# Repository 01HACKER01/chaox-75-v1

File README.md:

# chaox-75-v1

## What is this
This is a keyboard based on rp2040 with only wired connection and it has 82 keys and a rotary encoder.

## Why does this exits
i have a evofox keyboard which costs $10 i got it from a friend i used it for a long time but now teh keys sometimes doesnt work or doesnt press or something and i thought that lets make a keyboard so thats how this keyboard came to light. 

## How to assemble
u just have to solder all the things to the pcb and for that u will need a hot air gun for smalll capacittors and the mcu and a soldering iron to solder all the switches and rotary encoder.

## How to flash 
1. plug in your RP2040 board while holding the BOOT button.

2. Drag and drop the official Pico .uf2 firmware into the RPI-RP2 drive.
to check if this worked check The drive will reboot and reappears as CIRCUITPY.

3. Copy the kmk folder and main.py script from teh firmware folder straight into the root of CIRCUITPY.

thats it done. 

## Bill of Materials (BOM)

| Part | Qty | Approx. USD | Link |
|---|---:|---:|---|
| **RP2040 MCU** (QFN-56) | 1 | $1.20 | [Alibaba](https://www.alibaba.com/trade/search?SearchText=RP2040+QFN56) |
| **W25Q16JV SPI Flash** (SOIC-8) | 1 | $0.40 | [Alibaba](https://www.alibaba.com/trade/search?SearchText=W25Q16JV) |
| **MCP1700-3302E** 3.3V LDO | 1 | $0.35 | [Alibaba](https://www.alibaba.com/trade/search?SearchText=MCP1700T-3302E) |
| **12 MHz SMD Crystal** (3225 4-pin) | 1 | $0.25 | [Alibaba](https://www.alibaba.com/trade/search?SearchText=12MHz+3225+crystal) |
| **Type-C 16-Pin Receptacle** | 1 | $0.30 | [Alibaba](https://www.alibaba.com/trade/search?SearchText=USB-C+16P+receptacle) |
| **Kailh MX Hot-Swap Sockets** | 82 | $6.50 | [Alibaba](https://www.alibaba.com/trade/search?SearchText=Kailh+MX+hot+swap+socket) |
| **SK6812 MINI-E RGB LEDs** | 82 | $6.00 | [Alibaba](https://www.alibaba.com/trade/search?SearchText=SK6812MINI-E) |
| **1N4148W Switching Diodes** (SOD-123) | 82 | $1.50 | [Alibaba](https://www.alibaba.com/trade/search?SearchText=1N4148W+SOD-123) |
| **Passives (0603 Caps & Resistors)** | ~88 pcs | $2.50 | [Alibaba](https://www.alibaba.com/trade/search?SearchText=0603+smd+resistor+capacitor+pack) |
| **EC11 Rotary Encoder + Knob** | 1 | $1.00 | [Alibaba](https://www.alibaba.com/trade/search?SearchText=EC11+rotary+encoder) |
| **SMD Tactile Push Buttons** (Reset/Boot) | 2 | $0.30 | [Alibaba](https://www.alibaba.com/trade/search?SearchText=SMD+tactile+push+button) |
| **Mechanical Switches (82-90 pcs pack)** | 1 pack (90 pcs) | $20.00–$32.00 | [Alibaba](https://www.alibaba.com/trade/search?SearchText=Gateron+Kailh+switches+90pcs) |
| **82-Key Compatible Keycap Set** | 1 set | $15.00–$25.00 | [Alibaba](https://www.alibaba.com/trade/search?SearchText=75+percent+keycaps) |
| **Plate/PCB-Mount Stabilizers** (3x 2u, 1x 6.25u) | 1 set | $4.00–$8.00 | [Alibaba](https://www.alibaba.com/trade/search?SearchText=keyboard+stabilizers+set) |
| **Custom PCB Fabrication** (5 pcs, JLCPCB 2-layer) | 5 pcs | $15.00–$25.00 | [JLCPCB](https://jlcpcb.com) |
| **Case & Switch Plate** (3D printed / CNC / Acrylic stack) | 1 | $15.00–$35.00 | [JLCPCB 3D Print](https://jlcpcb.com/3d-printing) |

### 💰 Total Cost Breakdown

| Category | Estimated Cost |
|---|---:|
| **PCB Components & Electronics** | ~$20 |
| **Switches (82 pcs), Keycaps & Stabs** | ~$40–$65 |
| **PCB Fab (JLCPCB + shipping)** | ~$15–$25 |
| **Case & Switch Plate (3D Printed / CNC)** | ~$15–$35 |
| **Total Build Cost** | **~$90–$200** |

## END
i guess thats it so thank you bye

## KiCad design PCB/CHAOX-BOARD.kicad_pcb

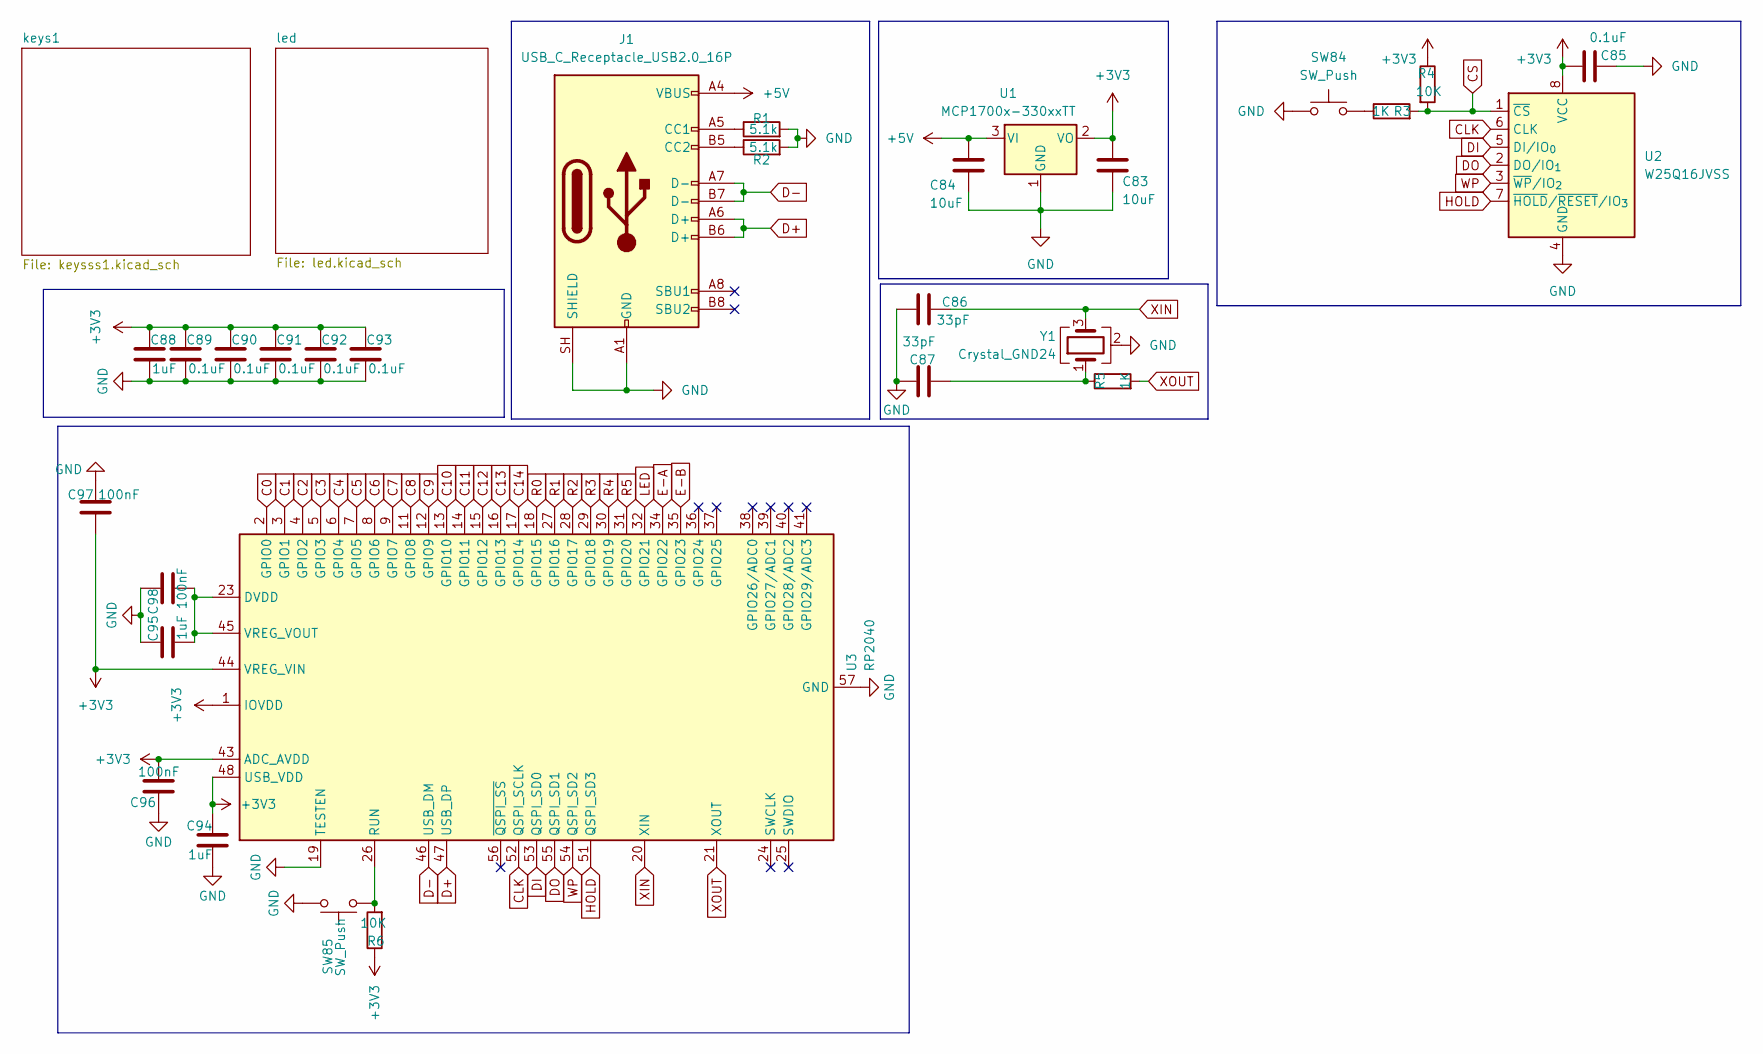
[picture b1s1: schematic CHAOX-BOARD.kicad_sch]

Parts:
C83, C84: 10uF; C_0603_1608Metric
C85, C89, C90, C91, C92, C93: 0.1uF; C_0603_1608Metric
C86, C87: 33pF; C_0603_1608Metric
C88, C94, C95: 1uF; C_0603_1608Metric
C96, C97, C98: 100nF; C_0603_1608Metric
J1: USB_C_Receptacle_USB2.0_16P; USB_C_Receptacle_GCT_USB4105-xx-A_16P_TopMnt_Horizontal
R1, R2: 5.1k; R_0603_1608Metric
R3, R5: 1K; R_0603_1608Metric
R4, R6: 10K; R_0603_1608Metric
SW84, SW85: SW_Push; SW_PUSH_6mm_H5mm
U1: MCP1700x-330xxTT; SOT-23
U2: W25Q16JVSS; SOIC-8_3.9x4.9mm_P1.27mm
U3: RP2040; QFN-56-1EP_7x7mm_P0.4mm_EP3.2x3.2mm
Y1: Crystal_GND24; Crystal_SMD_3225-4Pin_3.2x2.5mm

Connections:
+3V3: C83.1, C85.1, C88.1, C89.1, C90.1, C91.1, C92.1, C93.1, C94.1, C96.2, C97.2, R4.1, R6.1, U1.2 (VO), U2.8 (VCC), U3.1 (IOVDD), U3.10 (IOVDD), U3.22 (IOVDD), U3.33 (IOVDD), U3.42 (IOVDD), U3.43 (ADC_AVDD), U3.44 (VREG_VIN), U3.48 (USB_VDD), U3.49 (IOVDD)
+5V: C84.1, J1.A4 (VBUS), J1.A9 (VBUS), J1.B4 (VBUS), J1.B9 (VBUS), U1.3 (VI); also elsewhere on the board
C0: U3.2 (GPIO0); also elsewhere on the board
C1: U3.3 (GPIO1); also elsewhere on the board
C2: U3.4 (GPIO2); also elsewhere on the board
C3: U3.5 (GPIO3); also elsewhere on the board
C4: U3.6 (GPIO4); also elsewhere on the board
C5: U3.7 (GPIO5); also elsewhere on the board
C6: U3.8 (GPIO6); also elsewhere on the board
C7: U3.9 (GPIO7); also elsewhere on the board
C8: U3.11 (GPIO8); also elsewhere on the board
C9: U3.12 (GPIO9); also elsewhere on the board
C10: U3.13 (GPIO10); also elsewhere on the board
C11: U3.14 (GPIO11); also elsewhere on the board
C12: U3.15 (GPIO12); also elsewhere on the board
C13: U3.16 (GPIO13); also elsewhere on the board
C14: U3.17 (GPIO14); also elsewhere on the board
CLK: U2.6 (CLK), U3.52 (QSPI_SCLK)
CS: R3.2, R4.2, U2.1 (~CS)
D+: J1.A6 (D+), J1.B6 (D+), U3.47 (USB_DP)
D-: J1.A7 (D-), J1.B7 (D-), U3.46 (USB_DM)
DI: U2.5 (DI/IO_{0}), U3.53 (QSPI_SD0)
DO: U2.2 (DO/IO_{1}), U3.55 (QSPI_SD1)
E-A: U3.34 (GPIO22); also elsewhere on the board
E-B: U3.35 (GPIO23); also elsewhere on the board
E-SW2: U3.18 (GPIO15); also elsewhere on the board
GND: C83.2, C84.2, C85.2, C86.2, C87.2, C88.2, C89.2, C90.2, C91.2, C92.2, C93.2, C94.2, C95.1, C96.1, C97.1, C98.1, J1.A1 (GND), J1.A12 (GND), J1.B1 (GND), J1.B12 (GND), J1.SH (SHIELD), R1.2, R2.2, SW84.1, SW85.2, U1.1 (GND), U2.4 (GND), U3.19 (TESTEN), U3.57 (GND), Y1.2 (G), Y1.4 (G); also elsewhere on the board
HOLD: U2.7 (~HOLD/~RESET/IO_{3}), U3.51 (QSPI_SD3)
LED: U3.32 (GPIO21); also elsewhere on the board
unnamed: C87.1, R5.1, Y1.1
unnamed: J1.A5 (CC1), R1.1
unnamed: J1.B5 (CC2), R2.1
unnamed: R3.1, SW84.2
unnamed: R6.2, SW85.1, U3.26 (RUN)
unnamed: C95.2, C98.2, U3.23 (DVDD), U3.45 (VREG_VOUT), U3.50 (DVDD)
R1: U3.27 (GPIO16); also elsewhere on the board
R2: U3.28 (GPIO17); also elsewhere on the board
R3: U3.29 (GPIO18); also elsewhere on the board
R4: U3.30 (GPIO19); also elsewhere on the board
R5: U3.31 (GPIO20); also elsewhere on the board
WP: U2.3 (~WP/IO_{2}), U3.54 (QSPI_SD2)
XIN: C86.1, U3.20 (XIN), Y1.3
XOUT: R5.2, U3.21 (XOUT)

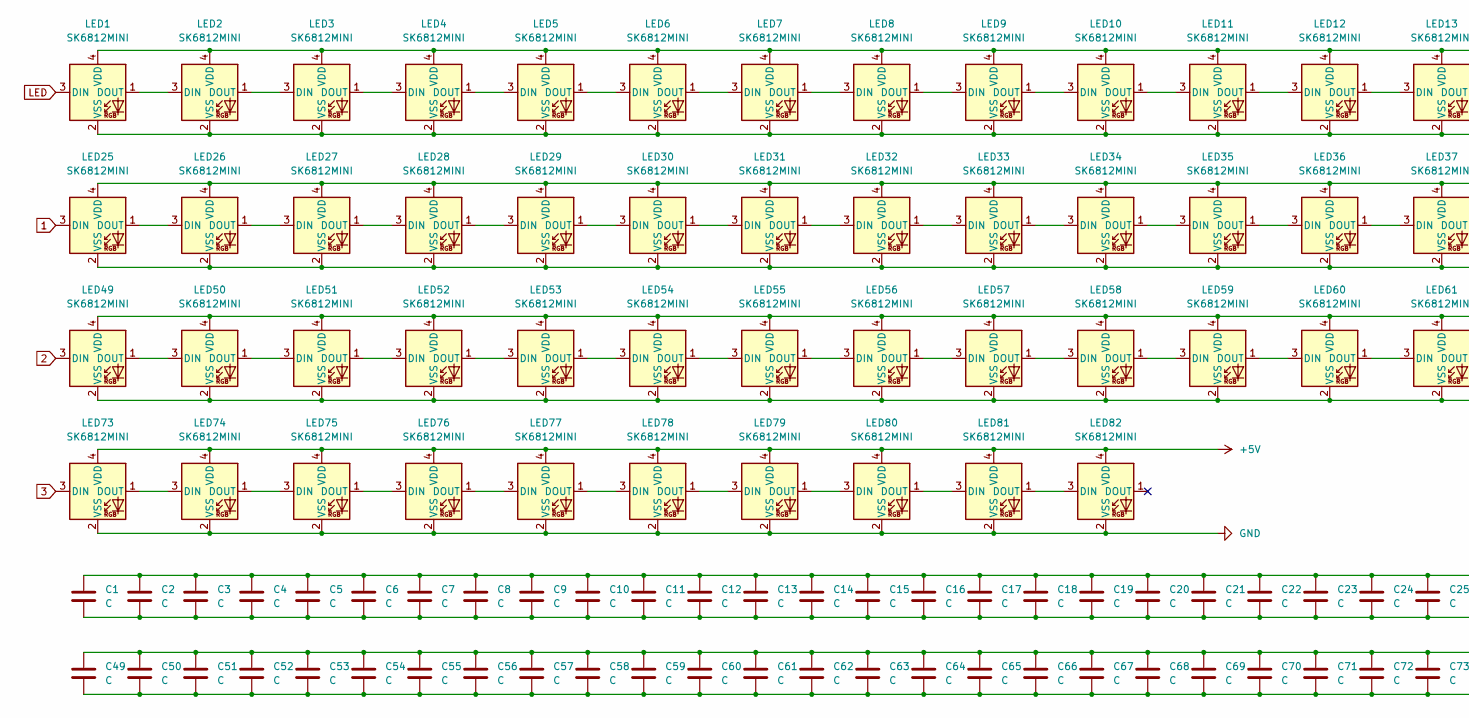
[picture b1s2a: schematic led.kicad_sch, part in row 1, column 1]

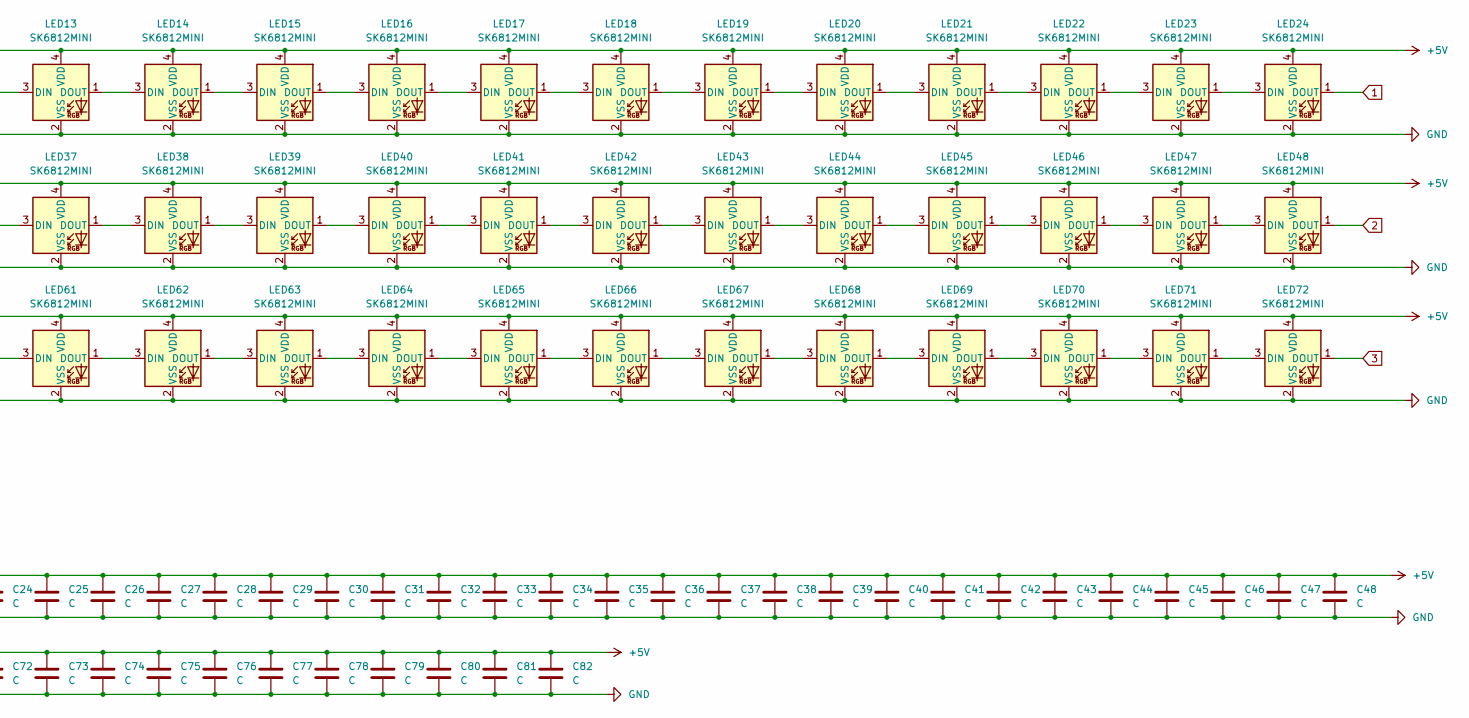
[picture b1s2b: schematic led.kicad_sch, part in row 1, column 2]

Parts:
C1, C2, C3, C4, C5, C6, C7, C8, C9, C10, C11, C12, C13, C14, C15, C16, C17, C18, C19, C20, C21, C22, C23, C24, C25, C26, C27, C28, C29, C30, C31, C32, C33, C34, C35, C36, C37, C38, C39, C40, C41, C42, C43, C44, C45, C46, C47, C48, C49, C50, C51, C52, C53, C54, C55, C56, C57, C58, C59, C60, C61, C62, C63, C64, C65, C66, C67, C68, C69, C70, C71, C72, C73, C74, C75, C76, C77, C78, C79, C80, C81, C82: C; C_0603_1608Metric
LED1, LED2, LED3, LED4, LED5, LED6, LED7, LED8, LED9, LED10, LED11, LED12, LED13, LED14, LED15, LED16, LED17, LED18, LED19, LED20, LED21, LED22, LED23, LED24, LED25, LED26, LED27, LED28, LED29, LED30, LED31, LED32, LED33, LED34, LED35, LED36, LED37, LED38, LED39, LED40, LED41, LED42, LED43, LED44, LED45, LED46, LED47, LED48, LED49, LED50, LED51, LED52, LED53, LED54, LED55, LED56, LED57, LED58, LED59, LED60, LED61, LED62, LED63, LED64, LED65, LED66, LED67, LED68, LED69, LED70, LED71, LED72, LED73, LED74, LED75, LED76, LED77, LED78, LED79, LED80, LED81, LED82: SK6812MINI; MX_SK6812MINI-E

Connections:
1: LED24.1 (DOUT), LED25.3 (DIN)
2: LED48.1 (DOUT), LED49.3 (DIN)
3: LED72.1 (DOUT), LED73.3 (DIN)
+5V: C1.1, C2.1, C3.1, C4.1, C5.1, C6.1, C7.1, C8.1, C9.1, C10.1, C11.1, C12.1, C13.1, C14.1, C15.1, C16.1, C17.1, C18.1, C19.1, C20.1, C21.1, C22.1, C23.1, C24.1, C25.1, C26.1, C27.1, C28.1, C29.1, C30.1, C31.1, C32.1, C33.1, C34.1, C35.1, C36.1, C37.1, C38.1, C39.1, C40.1, C41.1, C42.1, C43.1, C44.1, C45.1, C46.1, C47.1, C48.1, C49.1, C50.1, C51.1, C52.1, C53.1, C54.1, C55.1, C56.1, C57.1, C58.1, C59.1, C60.1, C61.1, C62.1, C63.1, C64.1, C65.1, C66.1, C67.1, C68.1, C69.1, C70.1, C71.1, C72.1, C73.1, C74.1, C75.1, C76.1, C77.1, C78.1, C79.1, C80.1, C81.1, C82.1, LED1.4 (VDD), LED2.4 (VDD), LED3.4 (VDD), LED4.4 (VDD), LED5.4 (VDD), LED6.4 (VDD), LED7.4 (VDD), LED8.4 (VDD), LED9.4 (VDD), LED10.4 (VDD), LED11.4 (VDD), LED12.4 (VDD), LED13.4 (VDD), LED14.4 (VDD), LED15.4 (VDD), LED16.4 (VDD), LED17.4 (VDD), LED18.4 (VDD), LED19.4 (VDD), LED20.4 (VDD), LED21.4 (VDD), LED22.4 (VDD), LED23.4 (VDD), LED24.4 (VDD), LED25.4 (VDD), LED26.4 (VDD), LED27.4 (VDD), LED28.4 (VDD), LED29.4 (VDD), LED30.4 (VDD), LED31.4 (VDD), LED32.4 (VDD), LED33.4 (VDD), LED34.4 (VDD), LED35.4 (VDD), LED36.4 (VDD), LED37.4 (VDD), LED38.4 (VDD), LED39.4 (VDD), LED40.4 (VDD), LED41.4 (VDD), LED42.4 (VDD), LED43.4 (VDD), LED44.4 (VDD), LED45.4 (VDD), LED46.4 (VDD), LED47.4 (VDD), LED48.4 (VDD), LED49.4 (VDD), LED50.4 (VDD), LED51.4 (VDD), LED52.4 (VDD), LED53.4 (VDD), LED54.4 (VDD), LED55.4 (VDD), LED56.4 (VDD), LED57.4 (VDD), LED58.4 (VDD), LED59.4 (VDD), LED60.4 (VDD), LED61.4 (VDD), LED62.4 (VDD), LED63.4 (VDD), LED64.4 (VDD), LED65.4 (VDD), LED66.4 (VDD), LED67.4 (VDD), LED68.4 (VDD), LED69.4 (VDD), LED70.4 (VDD), LED71.4 (VDD), LED72.4 (VDD), LED73.4 (VDD), LED74.4 (VDD), LED75.4 (VDD), LED76.4 (VDD), LED77.4 (VDD), LED78.4 (VDD), LED79.4 (VDD), LED80.4 (VDD), LED81.4 (VDD), LED82.4 (VDD); also elsewhere on the board
GND: C1.2, C2.2, C3.2, C4.2, C5.2, C6.2, C7.2, C8.2, C9.2, C10.2, C11.2, C12.2, C13.2, C14.2, C15.2, C16.2, C17.2, C18.2, C19.2, C20.2, C21.2, C22.2, C23.2, C24.2, C25.2, C26.2, C27.2, C28.2, C29.2, C30.2, C31.2, C32.2, C33.2, C34.2, C35.2, C36.2, C37.2, C38.2, C39.2, C40.2, C41.2, C42.2, C43.2, C44.2, C45.2, C46.2, C47.2, C48.2, C49.2, C50.2, C51.2, C52.2, C53.2, C54.2, C55.2, C56.2, C57.2, C58.2, C59.2, C60.2, C61.2, C62.2, C63.2, C64.2, C65.2, C66.2, C67.2, C68.2, C69.2, C70.2, C71.2, C72.2, C73.2, C74.2, C75.2, C76.2, C77.2, C78.2, C79.2, C80.2, C81.2, C82.2, LED1.2 (VSS), LED2.2 (VSS), LED3.2 (VSS), LED4.2 (VSS), LED5.2 (VSS), LED6.2 (VSS), LED7.2 (VSS), LED8.2 (VSS), LED9.2 (VSS), LED10.2 (VSS), LED11.2 (VSS), LED12.2 (VSS), LED13.2 (VSS), LED14.2 (VSS), LED15.2 (VSS), LED16.2 (VSS), LED17.2 (VSS), LED18.2 (VSS), LED19.2 (VSS), LED20.2 (VSS), LED21.2 (VSS), LED22.2 (VSS), LED23.2 (VSS), LED24.2 (VSS), LED25.2 (VSS), LED26.2 (VSS), LED27.2 (VSS), LED28.2 (VSS), LED29.2 (VSS), LED30.2 (VSS), LED31.2 (VSS), LED32.2 (VSS), LED33.2 (VSS), LED34.2 (VSS), LED35.2 (VSS), LED36.2 (VSS), LED37.2 (VSS), LED38.2 (VSS), LED39.2 (VSS), LED40.2 (VSS), LED41.2 (VSS), LED42.2 (VSS), LED43.2 (VSS), LED44.2 (VSS), LED45.2 (VSS), LED46.2 (VSS), LED47.2 (VSS), LED48.2 (VSS), LED49.2 (VSS), LED50.2 (VSS), LED51.2 (VSS), LED52.2 (VSS), LED53.2 (VSS), LED54.2 (VSS), LED55.2 (VSS), LED56.2 (VSS), LED57.2 (VSS), LED58.2 (VSS), LED59.2 (VSS), LED60.2 (VSS), LED61.2 (VSS), LED62.2 (VSS), LED63.2 (VSS), LED64.2 (VSS), LED65.2 (VSS), LED66.2 (VSS), LED67.2 (VSS), LED68.2 (VSS), LED69.2 (VSS), LED70.2 (VSS), LED71.2 (VSS), LED72.2 (VSS), LED73.2 (VSS), LED74.2 (VSS), LED75.2 (VSS), LED76.2 (VSS), LED77.2 (VSS), LED78.2 (VSS), LED79.2 (VSS), LED80.2 (VSS), LED81.2 (VSS), LED82.2 (VSS); also elsewhere on the board
LED: LED1.3 (DIN); also elsewhere on the board
unnamed: LED1.1 (DOUT), LED2.3 (DIN)
unnamed: LED2.1 (DOUT), LED3.3 (DIN)
unnamed: LED3.1 (DOUT), LED4.3 (DIN)
unnamed: LED4.1 (DOUT), LED5.3 (DIN)
unnamed: LED5.1 (DOUT), LED6.3 (DIN)
unnamed: LED6.1 (DOUT), LED7.3 (DIN)
unnamed: LED7.1 (DOUT), LED8.3 (DIN)
unnamed: LED8.1 (DOUT), LED9.3 (DIN)
unnamed: LED9.1 (DOUT), LED10.3 (DIN)
unnamed: LED10.1 (DOUT), LED11.3 (DIN)
unnamed: LED11.1 (DOUT), LED12.3 (DIN)
unnamed: LED12.1 (DOUT), LED13.3 (DIN)
unnamed: LED13.1 (DOUT), LED14.3 (DIN)
unnamed: LED14.1 (DOUT), LED15.3 (DIN)
unnamed: LED15.1 (DOUT), LED16.3 (DIN)
unnamed: LED16.1 (DOUT), LED17.3 (DIN)
unnamed: LED17.1 (DOUT), LED18.3 (DIN)
unnamed: LED18.1 (DOUT), LED19.3 (DIN)
unnamed: LED19.1 (DOUT), LED20.3 (DIN)
unnamed: LED20.1 (DOUT), LED21.3 (DIN)
unnamed: LED21.1 (DOUT), LED22.3 (DIN)
unnamed: LED22.1 (DOUT), LED23.3 (DIN)
unnamed: LED23.1 (DOUT), LED24.3 (DIN)
unnamed: LED25.1 (DOUT), LED26.3 (DIN)
unnamed: LED26.1 (DOUT), LED27.3 (DIN)
unnamed: LED27.1 (DOUT), LED28.3 (DIN)
unnamed: LED28.1 (DOUT), LED29.3 (DIN)
unnamed: LED29.1 (DOUT), LED30.3 (DIN)
unnamed: LED30.1 (DOUT), LED31.3 (DIN)
unnamed: LED31.1 (DOUT), LED32.3 (DIN)
unnamed: LED32.1 (DOUT), LED33.3 (DIN)
unnamed: LED33.1 (DOUT), LED34.3 (DIN)
unnamed: LED34.1 (DOUT), LED35.3 (DIN)
unnamed: LED35.1 (DOUT), LED36.3 (DIN)
unnamed: LED36.1 (DOUT), LED37.3 (DIN)
unnamed: LED37.1 (DOUT), LED38.3 (DIN)
unnamed: LED38.1 (DOUT), LED39.3 (DIN)
unnamed: LED39.1 (DOUT), LED40.3 (DIN)
unnamed: LED40.1 (DOUT), LED41.3 (DIN)
unnamed: LED41.1 (DOUT), LED42.3 (DIN)
unnamed: LED42.1 (DOUT), LED43.3 (DIN)
unnamed: LED43.1 (DOUT), LED44.3 (DIN)
unnamed: LED44.1 (DOUT), LED45.3 (DIN)
unnamed: LED45.1 (DOUT), LED46.3 (DIN)
unnamed: LED46.1 (DOUT), LED47.3 (DIN)
unnamed: LED47.1 (DOUT), LED48.3 (DIN)
unnamed: LED49.1 (DOUT), LED50.3 (DIN)
unnamed: LED50.1 (DOUT), LED51.3 (DIN)
unnamed: LED51.1 (DOUT), LED52.3 (DIN)
unnamed: LED52.1 (DOUT), LED53.3 (DIN)
unnamed: LED53.1 (DOUT), LED54.3 (DIN)
unnamed: LED54.1 (DOUT), LED55.3 (DIN)
unnamed: LED55.1 (DOUT), LED56.3 (DIN)
unnamed: LED56.1 (DOUT), LED57.3 (DIN)
unnamed: LED57.1 (DOUT), LED58.3 (DIN)
unnamed: LED58.1 (DOUT), LED59.3 (DIN)
unnamed: LED59.1 (DOUT), LED60.3 (DIN)
unnamed: LED60.1 (DOUT), LED61.3 (DIN)
unnamed: LED61.1 (DOUT), LED62.3 (DIN)
unnamed: LED62.1 (DOUT), LED63.3 (DIN)
unnamed: LED63.1 (DOUT), LED64.3 (DIN)
unnamed: LED64.1 (DOUT), LED65.3 (DIN)
unnamed: LED65.1 (DOUT), LED66.3 (DIN)
unnamed: LED66.1 (DOUT), LED67.3 (DIN)
unnamed: LED67.1 (DOUT), LED68.3 (DIN)
unnamed: LED68.1 (DOUT), LED69.3 (DIN)
unnamed: LED69.1 (DOUT), LED70.3 (DIN)
unnamed: LED70.1 (DOUT), LED71.3 (DIN)
unnamed: LED71.1 (DOUT), LED72.3 (DIN)
unnamed: LED73.1 (DOUT), LED74.3 (DIN)
unnamed: LED74.1 (DOUT), LED75.3 (DIN)
unnamed: LED75.1 (DOUT), LED76.3 (DIN)
unnamed: LED76.1 (DOUT), LED77.3 (DIN)
unnamed: LED77.1 (DOUT), LED78.3 (DIN)
unnamed: LED78.1 (DOUT), LED79.3 (DIN)
unnamed: LED79.1 (DOUT), LED80.3 (DIN)
unnamed: LED80.1 (DOUT), LED81.3 (DIN)
unnamed: LED81.1 (DOUT), LED82.3 (DIN)

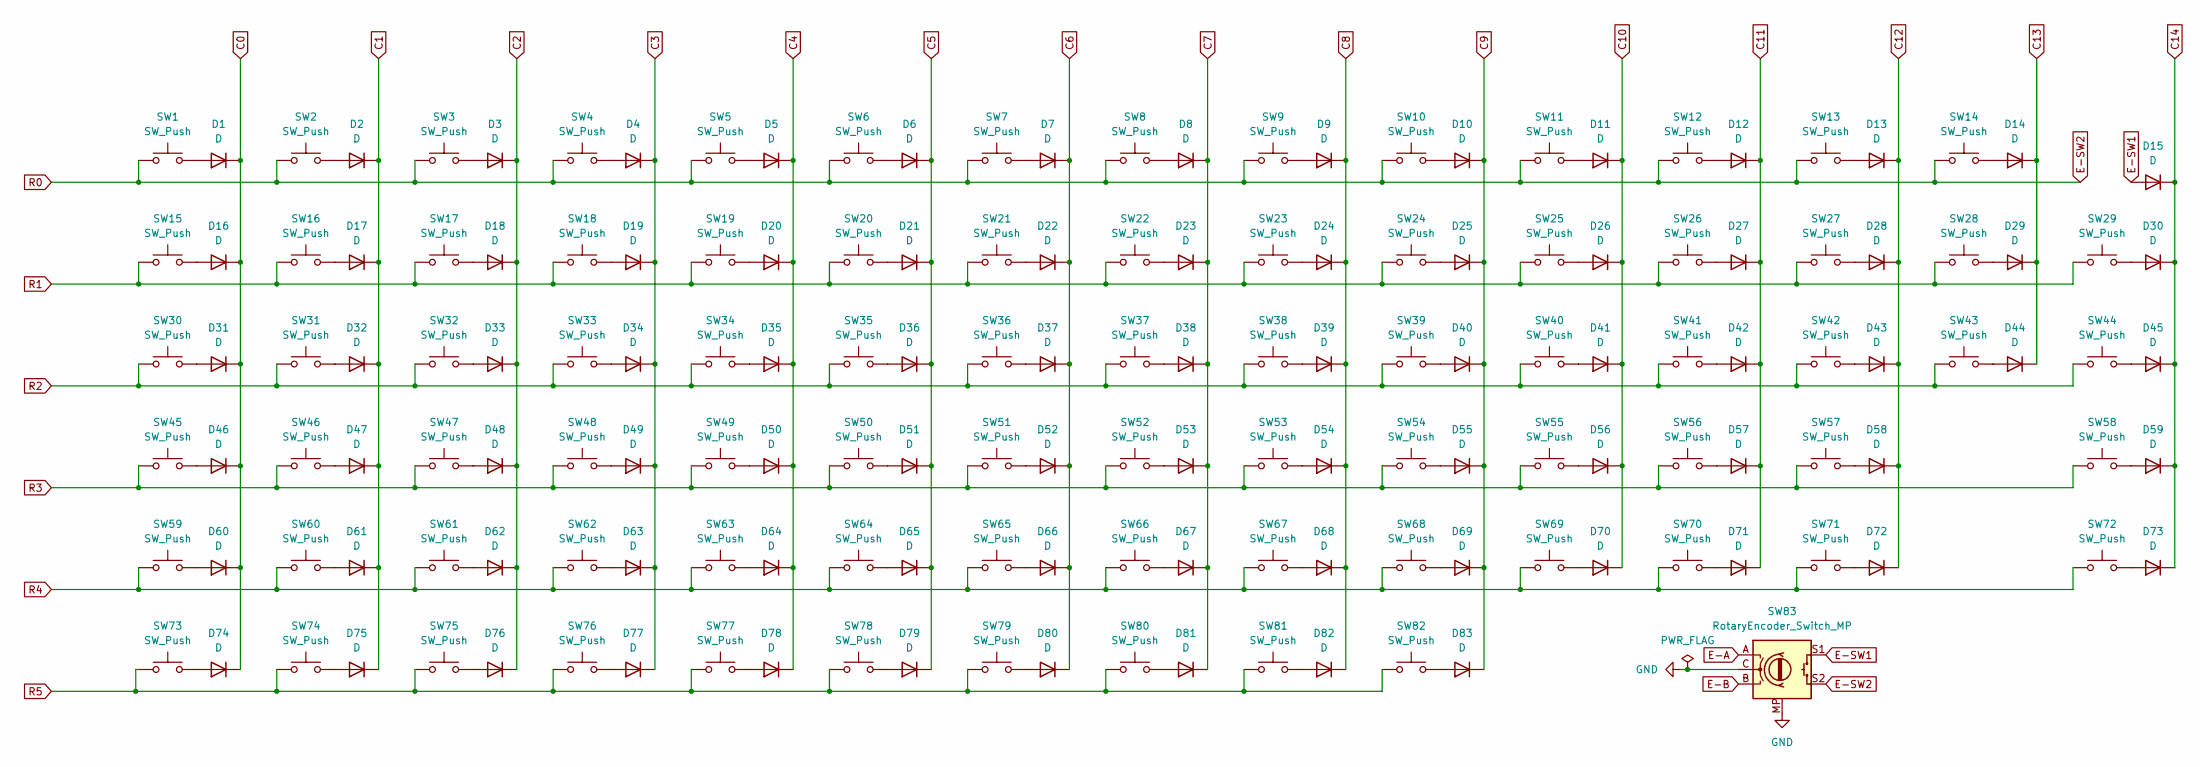
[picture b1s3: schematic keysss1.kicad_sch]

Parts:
D1, D2, D3, D4, D5, D6, D7, D8, D9, D10, D11, D12, D13, D14, D15, D16, D17, D18, D19, D20, D21, D22, D23, D24, D25, D26, D27, D28, D29, D30, D31, D32, D33, D34, D35, D36, D37, D38, D39, D40, D41, D42, D43, D44, D45, D46, D47, D48, D49, D50, D51, D52, D53, D54, D55, D56, D57, D58, D59, D60, D61, D62, D63, D64, D65, D66, D67, D68, D69, D70, D71, D72, D73, D74, D75, D76, D77, D78, D79, D80, D81, D82, D83: D; D_SOD-123
SW1, SW2, SW3, SW4, SW5, SW6, SW7, SW8, SW9, SW10, SW11, SW12, SW13, SW14, SW15, SW16, SW17, SW18, SW19, SW20, SW21, SW22, SW23, SW24, SW25, SW26, SW27, SW28, SW29, SW30, SW31, SW32, SW33, SW34, SW35, SW36, SW37, SW38, SW39, SW40, SW41, SW42, SW43, SW44, SW45, SW46, SW47, SW48, SW49, SW50, SW51, SW52, SW53, SW54, SW55, SW56, SW57, SW58, SW59, SW60, SW61, SW62, SW63, SW64, SW65, SW66, SW67, SW68, SW69, SW70, SW71, SW72, SW73, SW74, SW75, SW76, SW77, SW78, SW79, SW80, SW81, SW82: SW_Push; SW_Hotswap_Kailh_MX_1.00u
SW83: RotaryEncoder_Switch_MP; RotaryEncoder_Alps_EC11E-Switch_Vertical_H20mm

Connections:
C0: D1.1 (K), D16.1 (K), D31.1 (K), D46.1 (K), D60.1 (K), D74.1 (K); also elsewhere on the board
C1: D2.1 (K), D17.1 (K), D32.1 (K), D47.1 (K), D61.1 (K), D75.1 (K); also elsewhere on the board
C2: D3.1 (K), D18.1 (K), D33.1 (K), D48.1 (K), D62.1 (K), D76.1 (K); also elsewhere on the board
C3: D4.1 (K), D19.1 (K), D34.1 (K), D49.1 (K), D63.1 (K), D77.1 (K); also elsewhere on the board
C4: D5.1 (K), D20.1 (K), D35.1 (K), D50.1 (K), D64.1 (K), D78.1 (K); also elsewhere on the board
C5: D6.1 (K), D21.1 (K), D36.1 (K), D51.1 (K), D65.1 (K), D79.1 (K); also elsewhere on the board
C6: D7.1 (K), D22.1 (K), D37.1 (K), D52.1 (K), D66.1 (K), D80.1 (K); also elsewhere on the board
C7: D8.1 (K), D23.1 (K), D38.1 (K), D53.1 (K), D67.1 (K), D81.1 (K); also elsewhere on the board
C8: D9.1 (K), D24.1 (K), D39.1 (K), D54.1 (K), D68.1 (K), D82.1 (K); also elsewhere on the board
C9: D10.1 (K), D25.1 (K), D40.1 (K), D55.1 (K), D69.1 (K), D83.1 (K); also elsewhere on the board
C10: D11.1 (K), D26.1 (K), D41.1 (K), D56.1 (K), D70.1 (K); also elsewhere on the board
C11: D12.1 (K), D27.1 (K), D42.1 (K), D57.1 (K), D71.1 (K); also elsewhere on the board
C12: D13.1 (K), D28.1 (K), D43.1 (K), D58.1 (K), D72.1 (K); also elsewhere on the board
C13: D14.1 (K), D29.1 (K), D44.1 (K); also elsewhere on the board
C14: D15.1 (K), D30.1 (K), D45.1 (K), D59.1 (K), D73.1 (K); also elsewhere on the board
E-A: SW83.A; also elsewhere on the board
E-B: SW83.B; also elsewhere on the board
E-SW1: D15.2 (A), SW83.S1
E-SW2: SW1.1, SW2.1, SW3.1, SW4.1, SW5.1, SW6.1, SW7.1, SW8.1, SW9.1, SW10.1, SW11.1, SW12.1, SW13.1, SW14.1, SW83.S2; also elsewhere on the board
GND: SW83.C, SW83.MP; also elsewhere on the board
unnamed: D1.2 (A), SW1.2
unnamed: D2.2 (A), SW2.2
unnamed: D3.2 (A), SW3.2
unnamed: D4.2 (A), SW4.2
unnamed: D5.2 (A), SW5.2
unnamed: D6.2 (A), SW6.2
unnamed: D7.2 (A), SW7.2
unnamed: D8.2 (A), SW8.2
unnamed: D9.2 (A), SW9.2
unnamed: D10.2 (A), SW10.2
unnamed: D11.2 (A), SW11.2
unnamed: D12.2 (A), SW12.2
unnamed: D13.2 (A), SW13.2
unnamed: D14.2 (A), SW14.2
unnamed: D16.2 (A), SW15.2
unnamed: D17.2 (A), SW16.2
unnamed: D18.2 (A), SW17.2
unnamed: D19.2 (A), SW18.2
unnamed: D20.2 (A), SW19.2
unnamed: D21.2 (A), SW20.2
unnamed: D22.2 (A), SW21.2
unnamed: D23.2 (A), SW22.2
unnamed: D24.2 (A), SW23.2
unnamed: D25.2 (A), SW24.2
unnamed: D26.2 (A), SW25.2
unnamed: D27.2 (A), SW26.2
unnamed: D28.2 (A), SW27.2
unnamed: D29.2 (A), SW28.2
unnamed: D30.2 (A), SW29.2
unnamed: D31.2 (A), SW30.2
unnamed: D32.2 (A), SW31.2
unnamed: D33.2 (A), SW32.2
unnamed: D34.2 (A), SW33.2
unnamed: D35.2 (A), SW34.2
unnamed: D36.2 (A), SW35.2
unnamed: D37.2 (A), SW36.2
unnamed: D38.2 (A), SW37.2
unnamed: D39.2 (A), SW38.2
unnamed: D40.2 (A), SW39.2
unnamed: D41.2 (A), SW40.2
unnamed: D42.2 (A), SW41.2
unnamed: D43.2 (A), SW42.2
unnamed: D44.2 (A), SW43.2
unnamed: D45.2 (A), SW44.2
unnamed: D46.2 (A), SW45.2
unnamed: D47.2 (A), SW46.2
unnamed: D48.2 (A), SW47.2
unnamed: D49.2 (A), SW48.2
unnamed: D50.2 (A), SW49.2
unnamed: D51.2 (A), SW50.2
unnamed: D52.2 (A), SW51.2
unnamed: D53.2 (A), SW52.2
unnamed: D54.2 (A), SW53.2
unnamed: D55.2 (A), SW54.2
unnamed: D56.2 (A), SW55.2
unnamed: D57.2 (A), SW56.2
unnamed: D58.2 (A), SW57.2
unnamed: D59.2 (A), SW58.2
unnamed: D60.2 (A), SW59.2
unnamed: D61.2 (A), SW60.2
unnamed: D62.2 (A), SW61.2
unnamed: D63.2 (A), SW62.2
unnamed: D64.2 (A), SW63.2
unnamed: D65.2 (A), SW64.2
unnamed: D66.2 (A), SW65.2
unnamed: D67.2 (A), SW66.2
unnamed: D68.2 (A), SW67.2
unnamed: D69.2 (A), SW68.2
unnamed: D70.2 (A), SW69.2
unnamed: D71.2 (A), SW70.2
unnamed: D72.2 (A), SW71.2
unnamed: D73.2 (A), SW72.2
unnamed: D74.2 (A), SW73.2
unnamed: D75.2 (A), SW74.2
unnamed: D76.2 (A), SW75.2
unnamed: D77.2 (A), SW76.2
unnamed: D78.2 (A), SW77.2
unnamed: D79.2 (A), SW78.2
unnamed: D80.2 (A), SW79.2
unnamed: D81.2 (A), SW80.2
unnamed: D82.2 (A), SW81.2
unnamed: D83.2 (A), SW82.2
R1: SW15.1, SW16.1, SW17.1, SW18.1, SW19.1, SW20.1, SW21.1, SW22.1, SW23.1, SW24.1, SW25.1, SW26.1, SW27.1, SW28.1, SW29.1; also elsewhere on the board
R2: SW30.1, SW31.1, SW32.1, SW33.1, SW34.1, SW35.1, SW36.1, SW37.1, SW38.1, SW39.1, SW40.1, SW41.1, SW42.1, SW43.1, SW44.1; also elsewhere on the board
R3: SW45.1, SW46.1, SW47.1, SW48.1, SW49.1, SW50.1, SW51.1, SW52.1, SW53.1, SW54.1, SW55.1, SW56.1, SW57.1, SW58.1; also elsewhere on the board
R4: SW59.1, SW60.1, SW61.1, SW62.1, SW63.1, SW64.1, SW65.1, SW66.1, SW67.1, SW68.1, SW69.1, SW70.1, SW71.1, SW72.1; also elsewhere on the board
R5: SW73.1, SW74.1, SW75.1, SW76.1, SW77.1, SW78.1, SW79.1, SW80.1, SW81.1, SW82.1; also elsewhere on the board

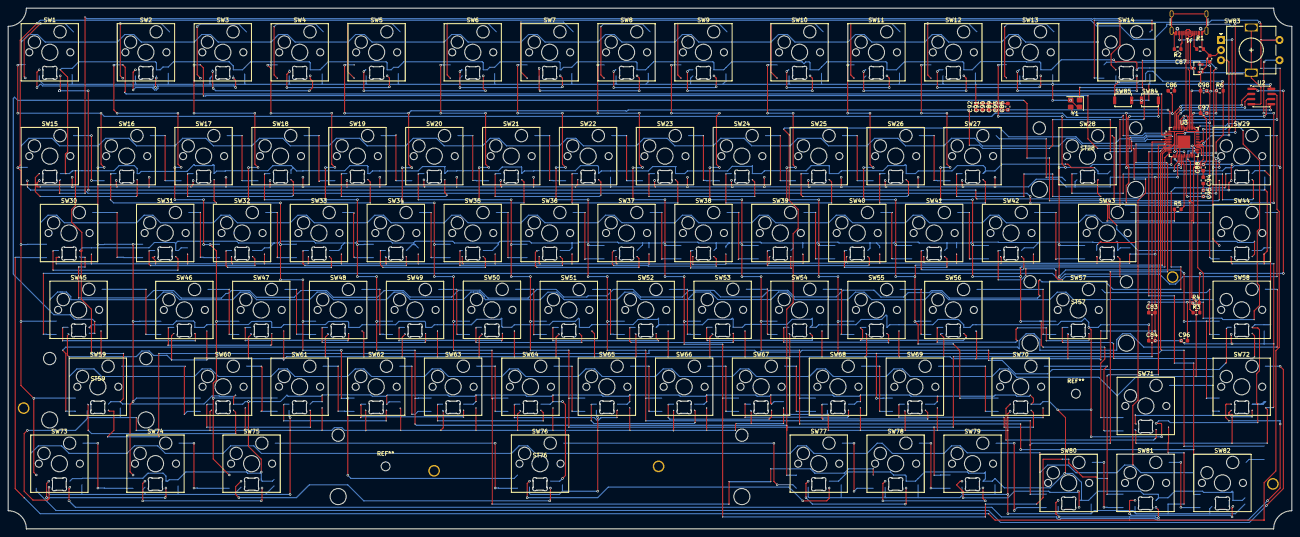
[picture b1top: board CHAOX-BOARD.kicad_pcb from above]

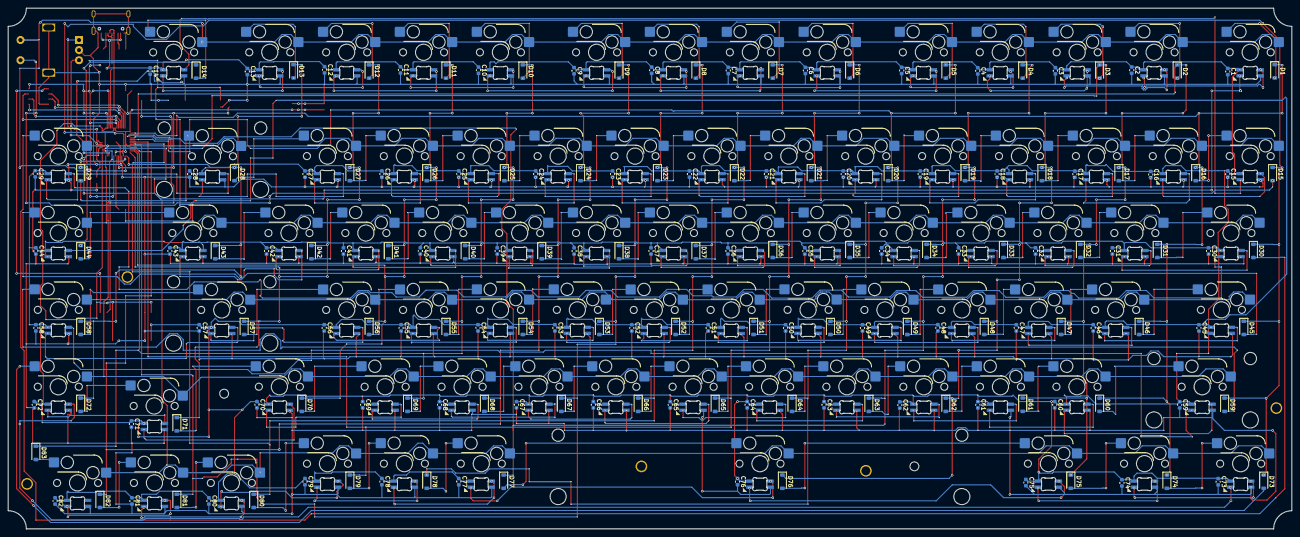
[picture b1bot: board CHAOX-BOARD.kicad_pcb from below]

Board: 2 copper layers, 318.0 x 129.0 mm, 363 parts (165 on the bottom side), 207 nets.

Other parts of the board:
ST28, ST57, ST59: MountingHole; Stabilizer_Cherry_MX_2.00u
ST76: MountingHole; Stabilizer_Cherry_MX_6.25u
